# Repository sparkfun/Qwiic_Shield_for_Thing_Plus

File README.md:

SparkFun Qwiic Shield for Thing Plus
========================================

[*SparkFun Qwiic Shield for Thing Plus (DEV-16138)*](https://www.sparkfun.com/products/16138)

This is a shield that connects the I<sup>2</sup>C bus on a development board using the Thing Plus footprint to four Qwiic connectors.

Repository Contents
-------------------

* **/Hardware** - Eagle design files (.brd, .sch)
* **/Production** - Production panel files (.brd)

Documentation
--------------

* **[Hookup Guide](https://learn.sparkfun.com/tutorials/sparkfun-qwiic-shield-for-thing-plus-hookup-guide)** - Basic hookup guide for the Qwiic Shield for Arduino Nano.
* **[SparkFun Fritzing repo](https://github.com/sparkfun/Fritzing_Parts)** - Fritzing diagrams for SparkFun products.
* **[SparkFun 3D Model repo](https://github.com/sparkfun/3D_Models)** - 3D models of SparkFun products. 
* **[SparkFun Graphical Datasheets](https://github.com/sparkfun/Graphical_Datasheets)** -Graphical Datasheets for various SparkFun products.

Product Versions
----------------

* [DEV-16138](https://www.sparkfun.com/products/16138)- An Arduino shield to connect the I<sup>2</sup>C bus on a Thing Plus (or compatible board) to Qwiic connectors. 

License Information
-------------------

This product is _**open source**_! 

Please review the LICENSE.md file for license information. 

If you have any questions or concerns on licensing, please contact technical support on our [SparkFun forums](https://forum.sparkfun.com/viewforum.php?f=152).

Distributed as-is; no warranty is given.

- Your friends at SparkFun.

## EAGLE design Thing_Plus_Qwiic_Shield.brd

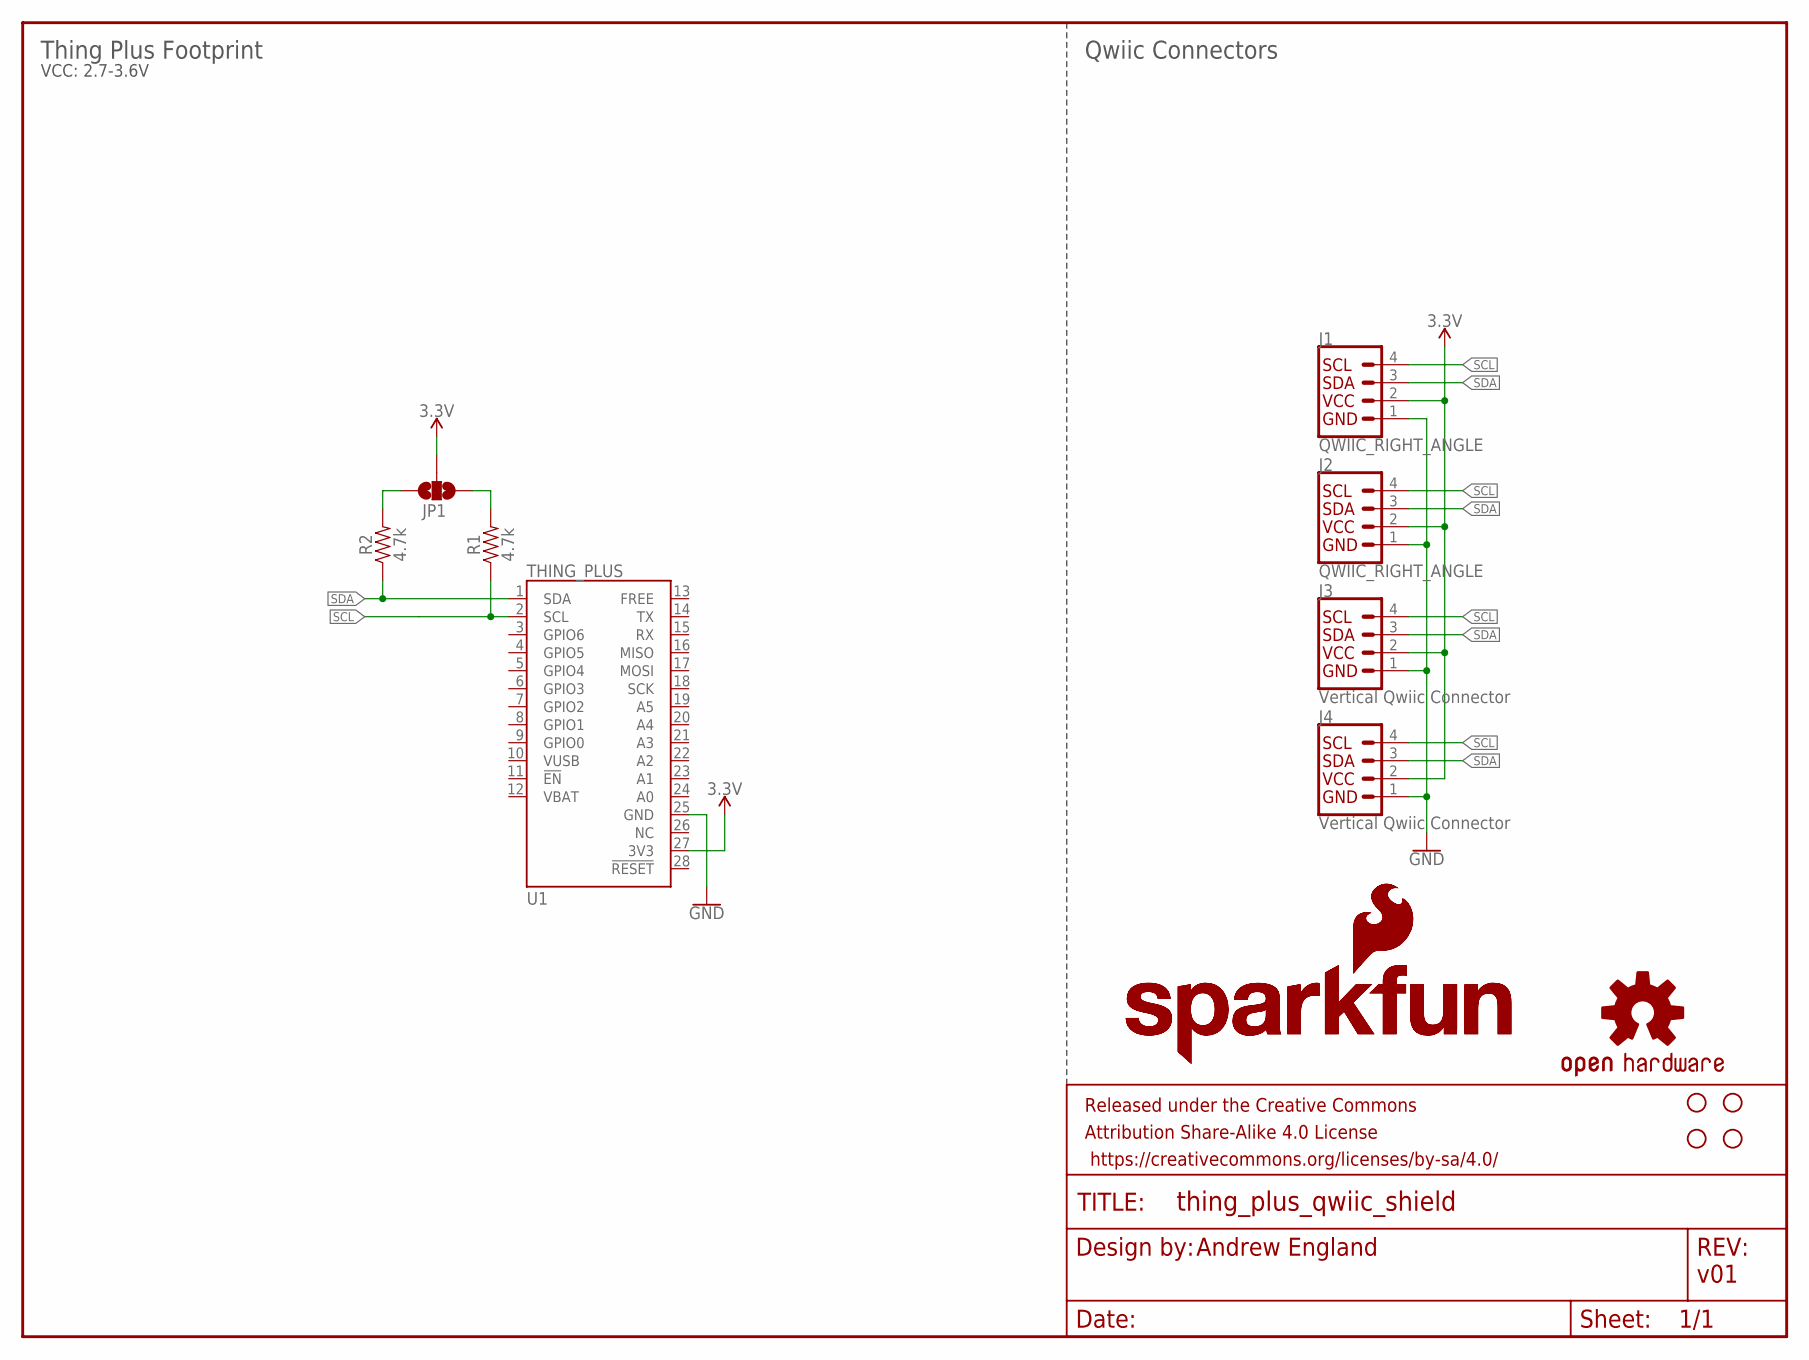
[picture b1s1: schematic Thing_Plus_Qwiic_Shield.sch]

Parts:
FRAME1: FRAME-LETTER; CREATIVE_COMMONS
H1, H2, H3, H4: STAND-OFF
J1, J2: QWIIC_RIGHT_ANGLE; JST04_1MM_RA
J3, J4: Vertical Qwiic Connector; JST04_1MM_VERT
JP1: JUMPER-SMT_3_NO_NO-SILK; SMT-JUMPER_3_NO_NO-SILK
LOGO1: SFE_LOGO_NAME_FLAME.1_INCH; SFE_LOGO_NAME_FLAME_.1
LOGO2: SFE_LOGO_NAME_FLAME.2_INCH; SFE_LOGO_NAME_FLAME_.2
LOGO3: OSHW-LOGOS; OSHW-LOGO-S
R1, R2: 4.7k; 0603
U1: THING_PLUS

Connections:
3.3V: J1.2, J2.2, J3.2, J4.2, JP1.2, U1.27 (3V3)
GND: J1.1, J2.1, J3.1, J4.1, U1.25 (GND)
unnamed: JP1.3, R2.2
unnamed: JP1.1, R1.2
SCL: J1.4, J2.4, J3.4, J4.4, R1.1, U1.2 (SCL)
SDA: J1.3, J2.3, J3.3, J4.3, R2.1, U1.1 (SDA)

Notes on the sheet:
Andrew England
v01
Thing Plus Footprint
Qwiic Connectors
VCC: 2.7-3.6V

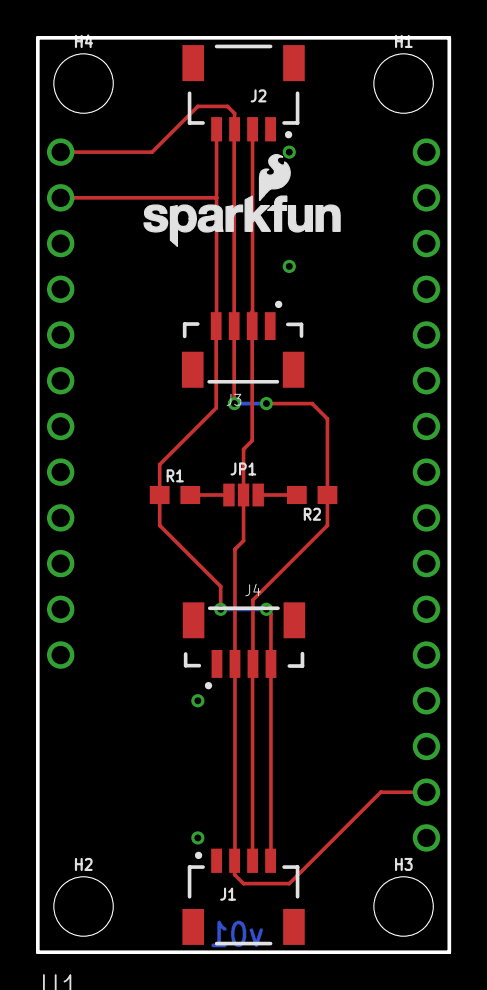
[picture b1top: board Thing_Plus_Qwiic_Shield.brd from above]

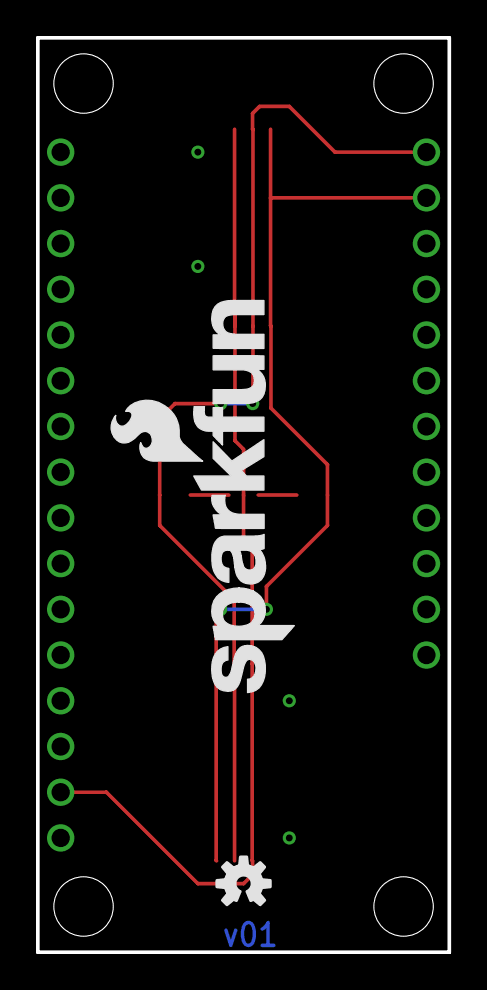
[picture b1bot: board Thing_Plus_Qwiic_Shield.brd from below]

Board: 2 copper layers, 22.9 x 50.8 mm, 16 parts (2 on the bottom side), 6 nets.

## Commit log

2019-12-10 initial layout and commit
2019-12-16 Initial latyout, run of checklist
2019-12-16 files weren't saved, saving and pushing...
2019-12-16 post-review changes
2019-12-23 panelizing and uploading gerbers
2020-01-29 Create README.md file
    Adding README file.
2020-01-29 Create .gitattributes
    Adding gitattributes file.
2020-01-29 Create .gitignore
    Adding gitignore file.
2020-01-29 removing .b## and .s##
2020-01-29 Rename Board File
2020-01-29 Rename Schematic File
2020-01-30 updating readme
2020-05-28 Update README
    Updating product photo for latest version and updating product versions.

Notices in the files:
parts and their libraries:
SparkFun-Aesthetics: Licensing: Creative Commons ShareAlike 4.0 International - https://creativecommons.org/licenses/by-sa/4.0
SparkFun-Aesthetics: Released under the Creative Commons Attribution Share-Alike 4.0 License
SparkFun-Aesthetics: https://creativecommons.org/licenses/by-sa/4.0
